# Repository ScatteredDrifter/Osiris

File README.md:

# Osiris - per-key-rgb macropad with functionality of a macropad
---

readme will be updated soon //

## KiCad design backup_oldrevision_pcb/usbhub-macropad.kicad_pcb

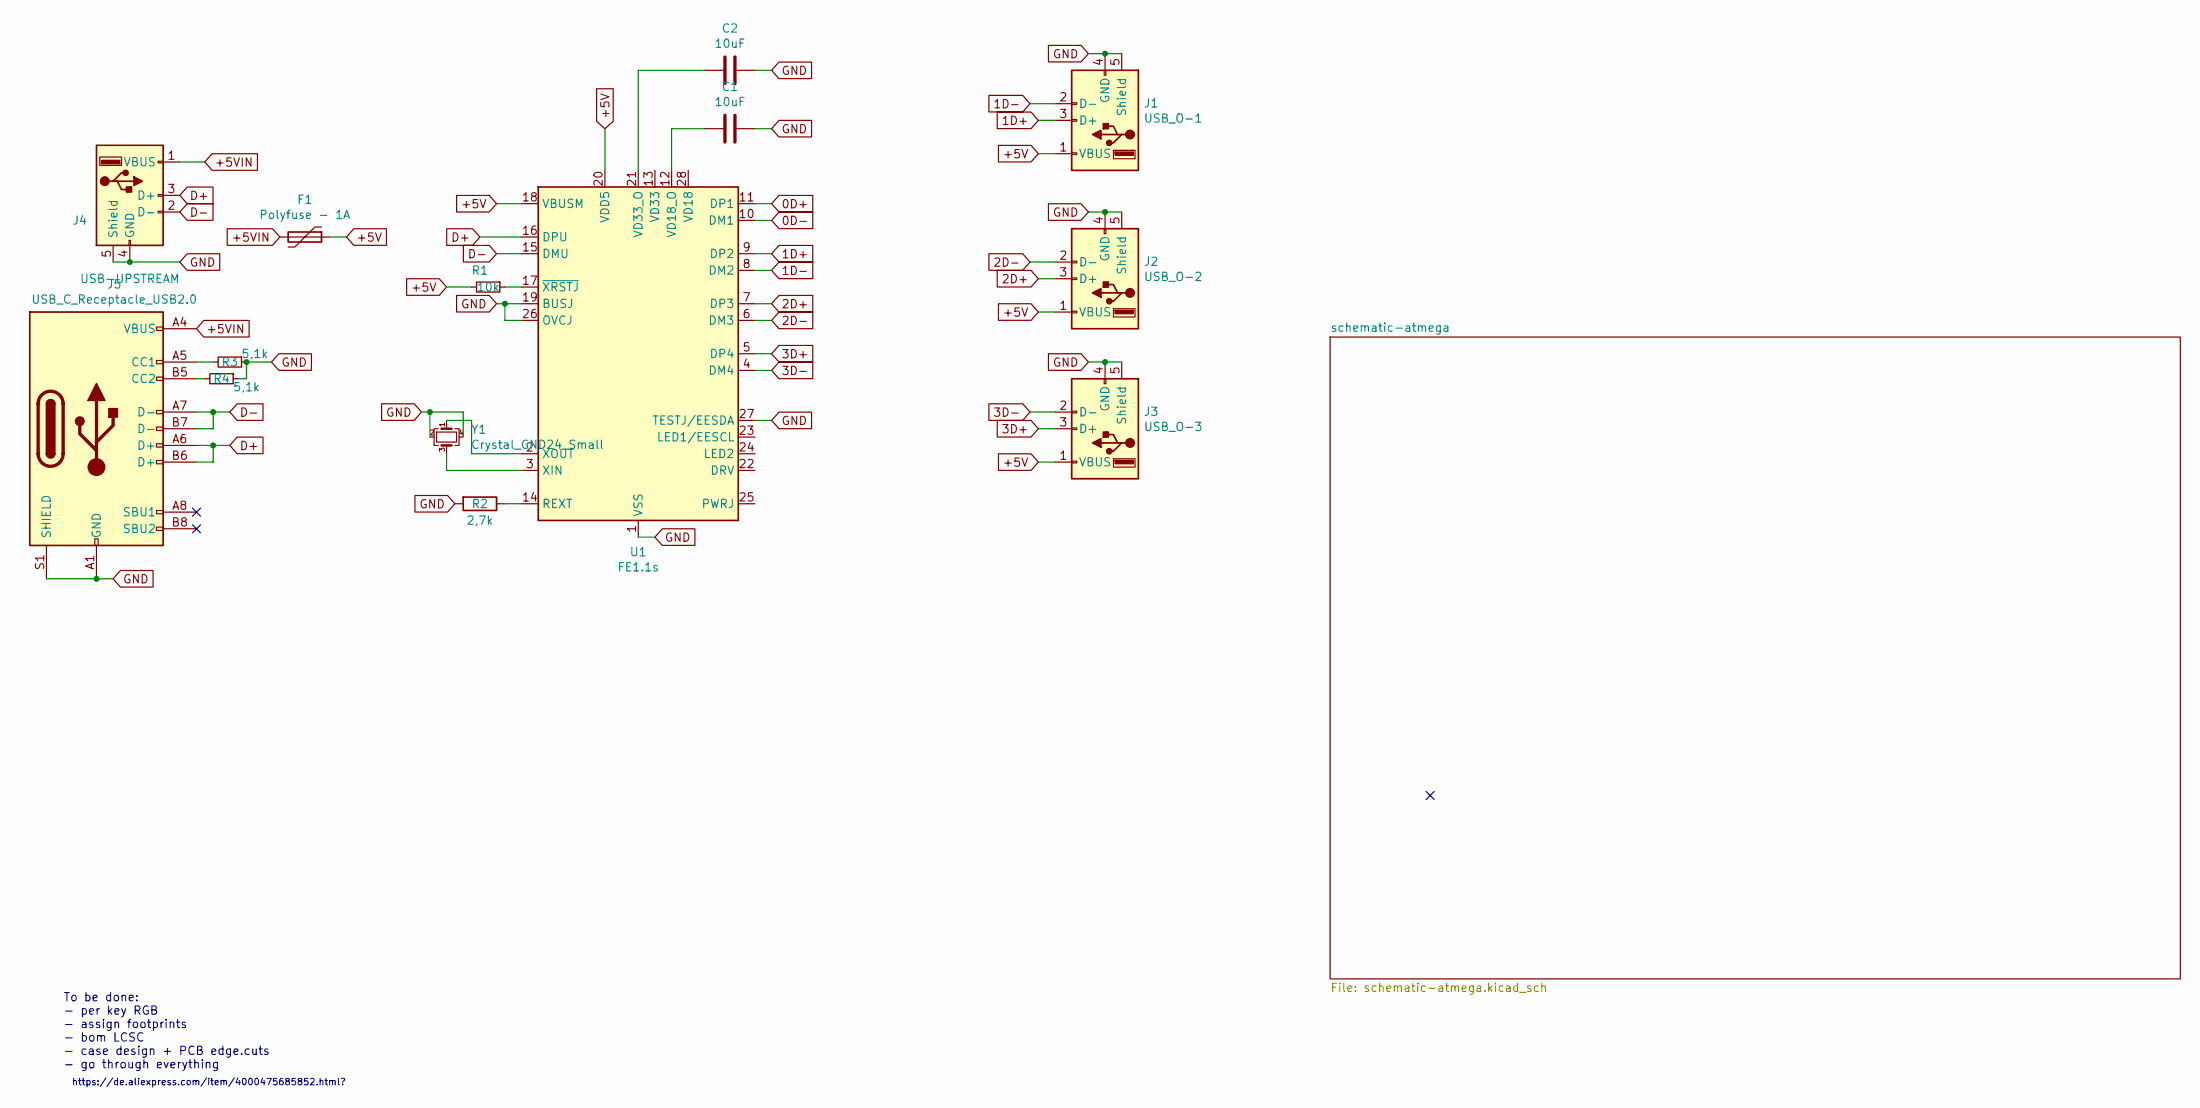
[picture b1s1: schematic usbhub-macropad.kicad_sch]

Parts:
C1, C2: 10uF; C_0805_2012Metric; LCSC C91245
F1: Polyfuse - 1A; Fuse_1206_3216Metric; LCSC C69688
J1: USB_O-1; GCT_USB1125-GF-B_REVA; LCSC C109354
J2: USB_O-2; GCT_USB1125-GF-B_REVA; LCSC C109354
J3: USB_O-3; GCT_USB1125-GF-B_REVA; LCSC C109354
J4: USB-UPSTREAM; GCT_USB1125-GF-B_REVA; LCSC C109354
J5: USB_C_Receptacle_USB2.0; USB_C_Receptacle_HRO_TYPE-C-31-M-12; LCSC C165948
R1: 10k; R_0805_2012Metric; LCSC C17414
R2: 2,7k; R_0805_2012Metric; LCSC C17530
R3, R4: 5,1k; R_0805_2012Metric; LCSC C26023
U1: FE1.1s; SSOP-28_3.9x9.9mm_P0.635mm; LCSC C9359
Y1: Crystal_GND24_Small; Crystal_SMD_3225-4Pin_3.2x2.5mm; LCSC C93234

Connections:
0D+: U1.11 (DP1); also elsewhere on the board
0D-: U1.10 (DM1); also elsewhere on the board
1D+: J1.3 (D+), U1.9 (DP2)
1D-: J1.2 (D-), U1.8 (DM2)
2D+: J2.3 (D+), U1.7 (DP3)
2D-: J2.2 (D-), U1.6 (DM3)
3D+: J3.3 (D+), U1.5 (DP4)
3D-: J3.2 (D-), U1.4 (DM4)
+5V: F1.1, J1.1 (VBUS), J2.1 (VBUS), J3.1 (VBUS), R1.2, U1.18 (VBUSM), U1.20 (VDD5); also elsewhere on the board
+5VIN: F1.2, J4.1 (VBUS), J5.A4 (VBUS), J5.A9 (VBUS), J5.B4 (VBUS), J5.B9 (VBUS)
D+: J4.3 (D+), J5.A6 (D+), J5.B6 (D+), U1.16 (DPU)
D-: J4.2 (D-), J5.A7 (D-), J5.B7 (D-), U1.15 (DMU)
GND: C1.1, C2.1, J1.4 (GND), J1.5 (Shield), J2.4 (GND), J2.5 (Shield), J3.4 (GND), J3.5 (Shield), J4.4 (GND), J4.5 (Shield), J5.A1 (GND), J5.A12 (GND), J5.B1 (GND), J5.B12 (GND), J5.S1 (SHIELD), R2.2, R3.1, R4.1, U1.1 (VSS), U1.19 (BUSJ), U1.26 (OVCJ), U1.27 (TESTJ/EESDA), Y1.2, Y1.4; also elsewhere on the board
unnamed: C1.2, U1.12 (VD18_O)
unnamed: C2.2, U1.21 (VD33_O)
unnamed: J5.A5 (CC1), R3.2
unnamed: J5.B5 (CC2), R4.2
unnamed: R1.1, U1.17 (~XRSTJ)
unnamed: R2.1, U1.14 (REXT)
unnamed: U1.2 (XOUT), Y1.1
unnamed: U1.3 (XIN), Y1.3

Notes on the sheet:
https://de.aliexpress.com/item/4000475685852.html?
To be done: - per key RGB - assign footprints - bom LCSC - case design + PCB edge.cuts - go through everything

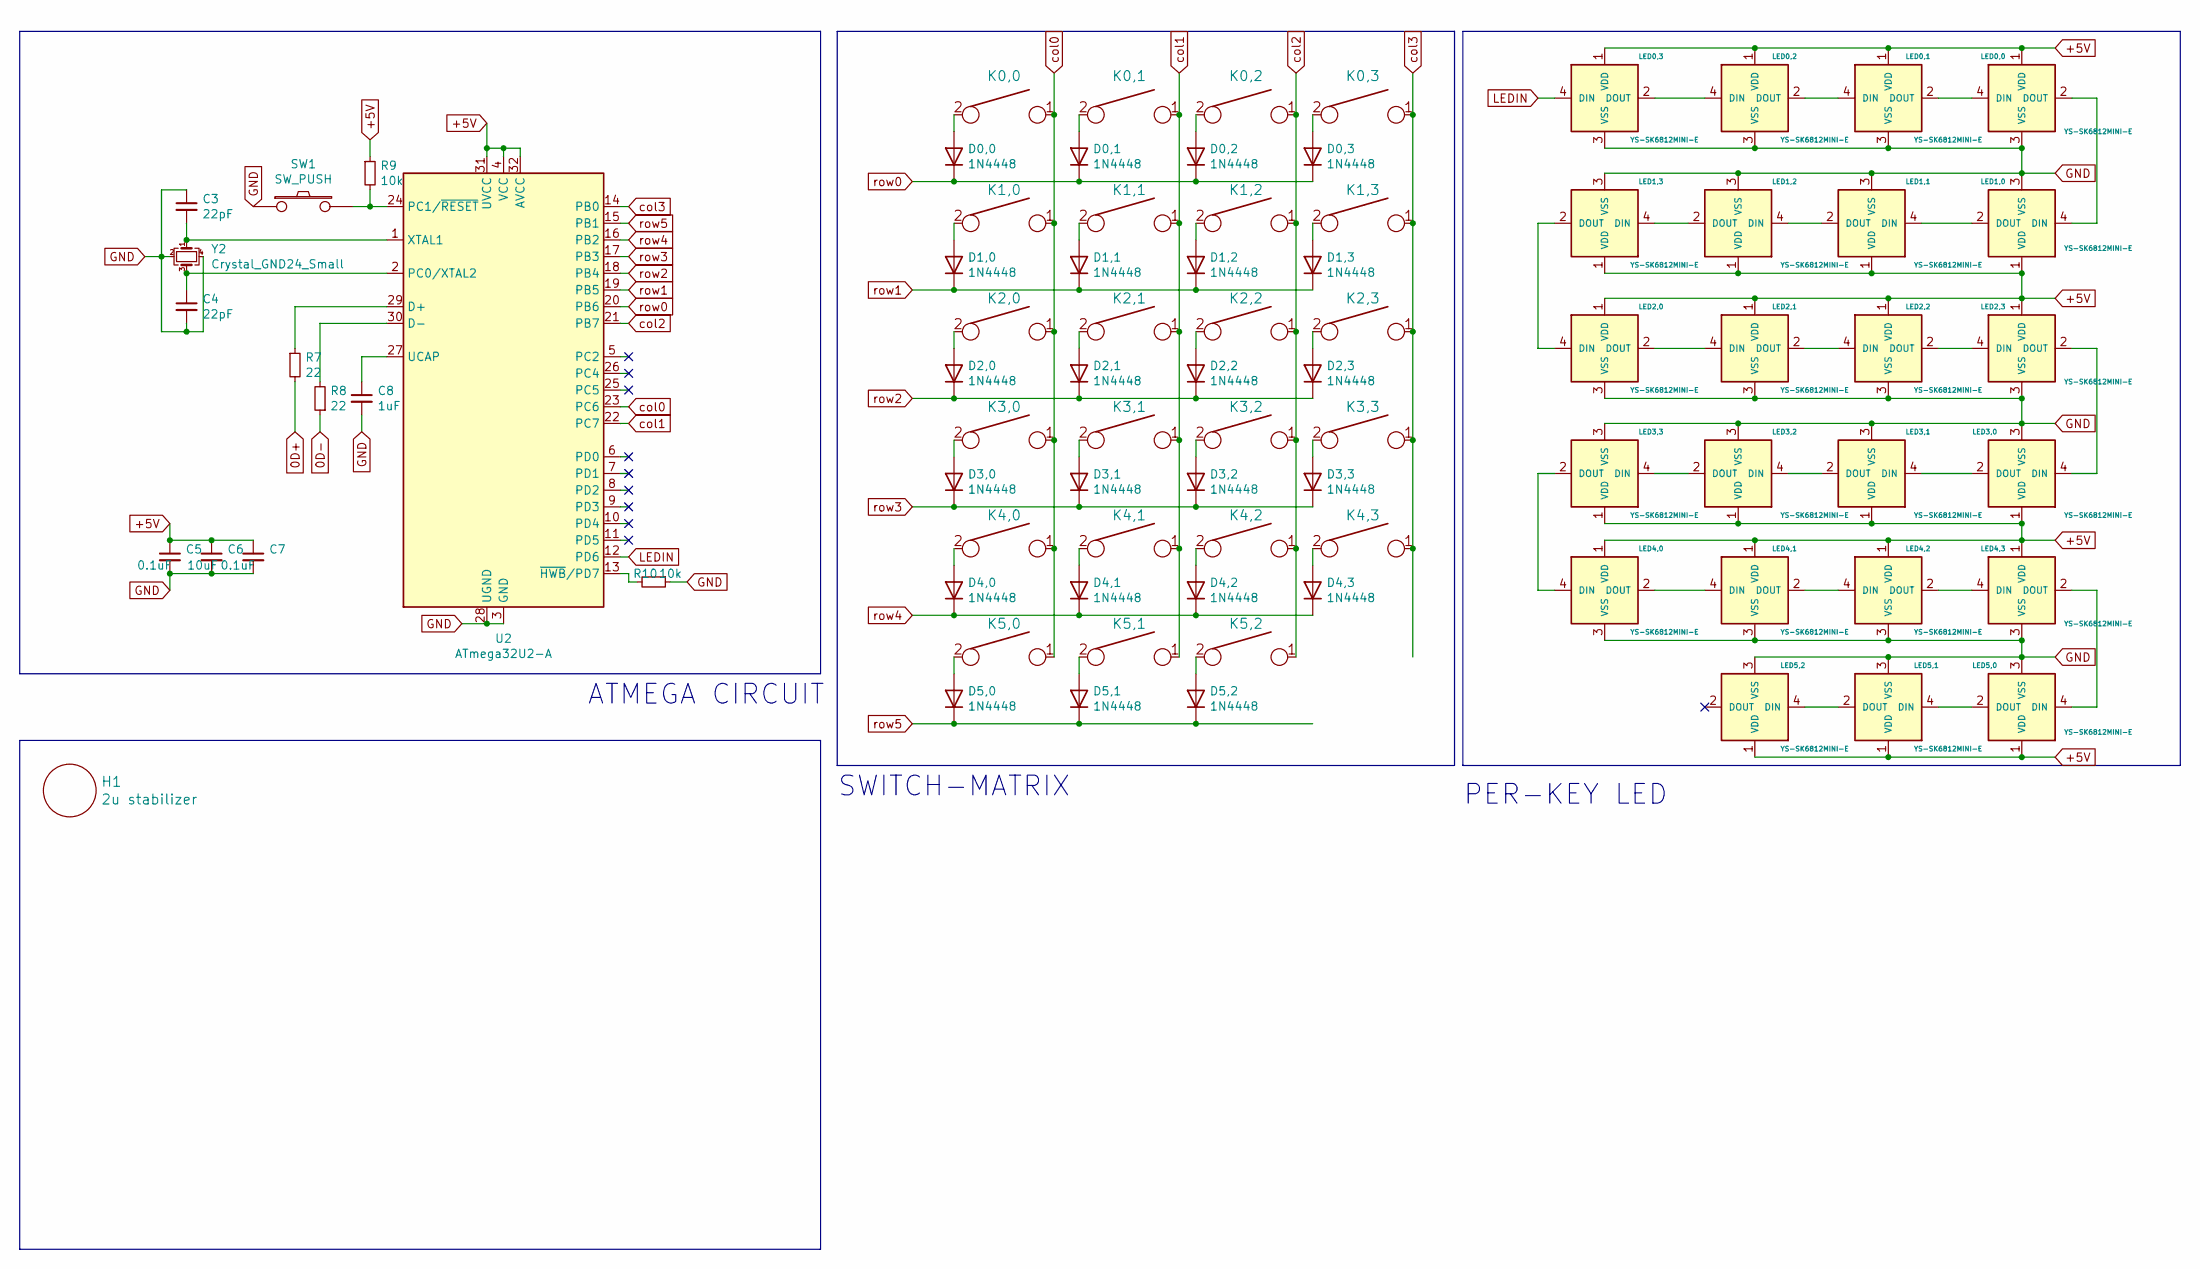
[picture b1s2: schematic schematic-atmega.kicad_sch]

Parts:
C3, C4: 22pF; C_0805_2012Metric; LCSC C1804
C5, C7: 0.1uF; C_0805_2012Metric; LCSC C49678
C6: 10uF; C_0805_2012Metric; LCSC C91245
C8: 1uF; C_0805_2012Metric; LCSC C28323
D0,0, D0,1, D0,2, D0,3, D1,0, D1,1, D1,2, D1,3, D2,0, D2,1, D2,2, D2,3, D3,0, D3,1, D3,2, D3,3, D4,0, D4,1, D4,2, D4,3, D5,0, D5,1, D5,2: 1N4448; D_SOD123; LCSC C2099
H1: 2u stabilizer; Stabilizer_MX_2u
K0,0, K0,1, K0,2, K0,3, K1,0, K1,1, K1,2, K1,3, K2,0, K2,1, K2,2, K2,3, K3,0, K3,1, K3,2, K3,3, K4,0, K4,1, K4,2, K4,3, K5,0, K5,1, K5,2: KEYSW; SW_MX
LED0,0, LED0,1, LED0,2, LED0,3, LED1,0, LED1,1, LED1,2, LED1,3, LED2,0, LED2,1, LED2,2, LED2,3, LED3,0, LED3,1, LED3,2, LED3,3, LED4,0, LED4,1, LED4,2, LED4,3, LED5,0, LED5,1, LED5,2: YS-SK6812MINI-E
R7, R8: 22; R_0805_2012Metric; LCSC C17561
R9, R10: 10k; R_0805_2012Metric; LCSC C17414
SW1: SW_PUSH; SW_SPST_TL3342; LCSC C318884
U2: ATmega32U2-A; TQFP-32_7x7mm_P0.8mm; LCSC C618733
Y2: Crystal_GND24_Small; Crystal_SMD_3225-4Pin_3.2x2.5mm; LCSC C13738

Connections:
0D+: R7.2; also elsewhere on the board
0D-: R8.1; also elsewhere on the board
+5V: C5.1, C6.1, C7.1, LED0,0.1 (VDD), LED0,1.1 (VDD), LED0,2.1 (VDD), LED0,3.1 (VDD), LED1,0.1 (VDD), LED1,1.1 (VDD), LED1,2.1 (VDD), LED1,3.1 (VDD), LED2,0.1 (VDD), LED2,1.1 (VDD), LED2,2.1 (VDD), LED2,3.1 (VDD), LED3,0.1 (VDD), LED3,1.1 (VDD), LED3,2.1 (VDD), LED3,3.1 (VDD), LED4,0.1 (VDD), LED4,1.1 (VDD), LED4,2.1 (VDD), LED4,3.1 (VDD), LED5,0.1 (VDD), LED5,1.1 (VDD), LED5,2.1 (VDD), R9.1, U2.4 (VCC), U2.31 (UVCC), U2.32 (AVCC); also elsewhere on the board
GND: C3.1, C4.2, C5.2, C6.2, C7.2, C8.2, LED0,0.3 (VSS), LED0,1.3 (VSS), LED0,2.3 (VSS), LED0,3.3 (VSS), LED1,0.3 (VSS), LED1,1.3 (VSS), LED1,2.3 (VSS), LED1,3.3 (VSS), LED2,0.3 (VSS), LED2,1.3 (VSS), LED2,2.3 (VSS), LED2,3.3 (VSS), LED3,0.3 (VSS), LED3,1.3 (VSS), LED3,2.3 (VSS), LED3,3.3 (VSS), LED4,0.3 (VSS), LED4,1.3 (VSS), LED4,2.3 (VSS), LED4,3.3 (VSS), LED5,0.3 (VSS), LED5,1.3 (VSS), LED5,2.3 (VSS), R10.1, SW1.1, U2.3 (GND), U2.28 (UGND), Y2.2, Y2.4; also elsewhere on the board
LEDIN: LED0,3.4 (DIN), U2.12 (PD6)
unnamed: C3.2, U2.1 (XTAL1), Y2.1
unnamed: C4.1, U2.2 (PC0/XTAL2), Y2.3
unnamed: C8.1, U2.27 (UCAP)
unnamed: D0,0.2 (A), K0,0.2
unnamed: D0,1.2 (A), K0,1.2
unnamed: D0,2.2 (A), K0,2.2
unnamed: D0,3.2 (A), K0,3.2
unnamed: D1,0.2 (A), K1,0.2
unnamed: D1,1.2 (A), K1,1.2
unnamed: D1,2.2 (A), K1,2.2
unnamed: D1,3.2 (A), K1,3.2
unnamed: D2,0.2 (A), K2,0.2
unnamed: D2,1.2 (A), K2,1.2
unnamed: D2,2.2 (A), K2,2.2
unnamed: D2,3.2 (A), K2,3.2
unnamed: D3,0.2 (A), K3,0.2
unnamed: D3,1.2 (A), K3,1.2
unnamed: D3,2.2 (A), K3,2.2
unnamed: D3,3.2 (A), K3,3.2
unnamed: D4,0.2 (A), K4,0.2
unnamed: D4,1.2 (A), K4,1.2
unnamed: D4,2.2 (A), K4,2.2
unnamed: D4,3.2 (A), K4,3.2
unnamed: D5,0.2 (A), K5,0.2
unnamed: D5,1.2 (A), K5,1.2
unnamed: D5,2.2 (A), K5,2.2
unnamed: LED0,0.2 (DOUT), LED1,0.4 (DIN)
unnamed: LED0,0.4 (DIN), LED0,1.2 (DOUT)
unnamed: LED0,1.4 (DIN), LED0,2.2 (DOUT)
unnamed: LED0,2.4 (DIN), LED0,3.2 (DOUT)
unnamed: LED1,0.2 (DOUT), LED1,1.4 (DIN)
unnamed: LED1,1.2 (DOUT), LED1,2.4 (DIN)
unnamed: LED1,2.2 (DOUT), LED1,3.4 (DIN)
unnamed: LED1,3.2 (DOUT), LED2,0.4 (DIN)
unnamed: LED2,0.2 (DOUT), LED2,1.4 (DIN)
unnamed: LED2,1.2 (DOUT), LED2,2.4 (DIN)
unnamed: LED2,2.2 (DOUT), LED2,3.4 (DIN)
unnamed: LED2,3.2 (DOUT), LED3,0.4 (DIN)
unnamed: LED3,0.2 (DOUT), LED3,1.4 (DIN)
unnamed: LED3,1.2 (DOUT), LED3,2.4 (DIN)
unnamed: LED3,2.2 (DOUT), LED3,3.4 (DIN)
unnamed: LED3,3.2 (DOUT), LED4,0.4 (DIN)
unnamed: LED4,0.2 (DOUT), LED4,1.4 (DIN)
unnamed: LED4,1.2 (DOUT), LED4,2.4 (DIN)
unnamed: LED4,2.2 (DOUT), LED4,3.4 (DIN)
unnamed: LED4,3.2 (DOUT), LED5,0.4 (DIN)
unnamed: LED5,0.2 (DOUT), LED5,1.4 (DIN)
unnamed: LED5,1.2 (DOUT), LED5,2.4 (DIN)
unnamed: R7.1, U2.29 (D+)
unnamed: R8.2, U2.30 (D-)
unnamed: R9.2, SW1.2, U2.24 (PC1/~RESET)
unnamed: R10.2, U2.13 (~HWB/PD7)
col0: K0,0.1, K1,0.1, K2,0.1, K3,0.1, K4,0.1, K5,0.1, U2.23 (PC6)
col1: K0,1.1, K1,1.1, K2,1.1, K3,1.1, K4,1.1, K5,1.1, U2.22 (PC7)
col2: K0,2.1, K1,2.1, K2,2.1, K3,2.1, K4,2.1, K5,2.1, U2.21 (PB7)
col3: K0,3.1, K1,3.1, K2,3.1, K3,3.1, K4,3.1, U2.14 (PB0)
row0: D0,0.1 (K), D0,1.1 (K), D0,2.1 (K), D0,3.1 (K), U2.20 (PB6)
row1: D1,0.1 (K), D1,1.1 (K), D1,2.1 (K), D1,3.1 (K), U2.19 (PB5)
row2: D2,0.1 (K), D2,1.1 (K), D2,2.1 (K), D2,3.1 (K), U2.18 (PB4)
row3: D3,0.1 (K), D3,1.1 (K), D3,2.1 (K), D3,3.1 (K), U2.17 (PB3)
row4: D4,0.1 (K), D4,1.1 (K), D4,2.1 (K), D4,3.1 (K), U2.16 (PB2)
row5: D5,0.1 (K), D5,1.1 (K), D5,2.1 (K), U2.15 (PB1)

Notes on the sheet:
ATMEGA CIRCUIT
PER-KEY LED
SWITCH-MATRIX

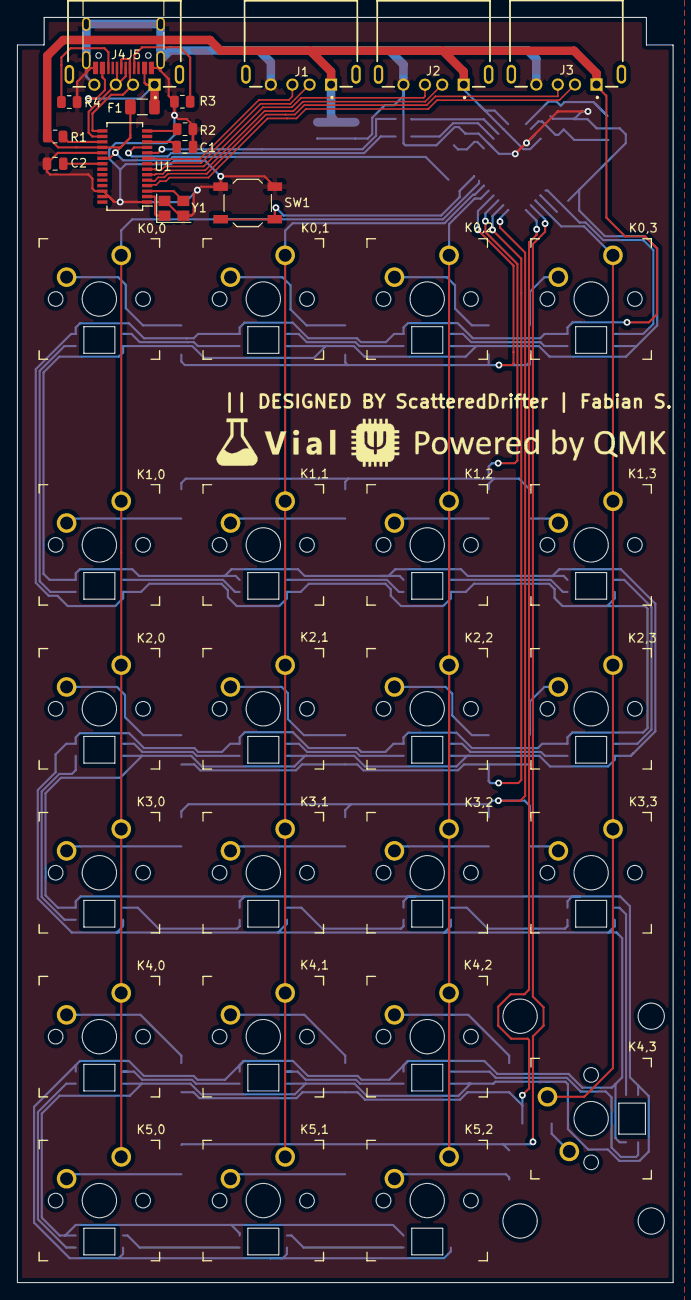
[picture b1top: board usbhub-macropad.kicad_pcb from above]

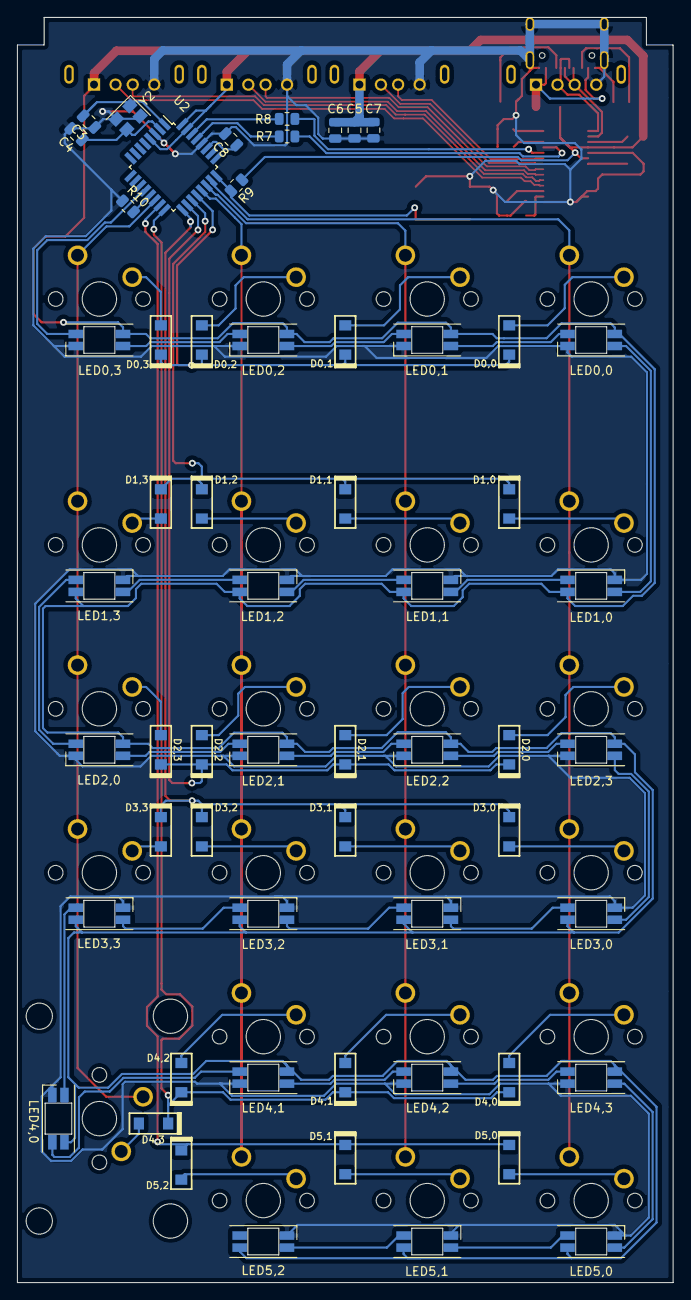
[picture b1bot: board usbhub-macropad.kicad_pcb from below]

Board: 2 copper layers, 76.2 x 147.0 mm, 97 parts (58 on the bottom side), 84 nets.

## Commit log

2022-01-15 initial commit, Pcb, base structure etc.
2022-01-15 added README
